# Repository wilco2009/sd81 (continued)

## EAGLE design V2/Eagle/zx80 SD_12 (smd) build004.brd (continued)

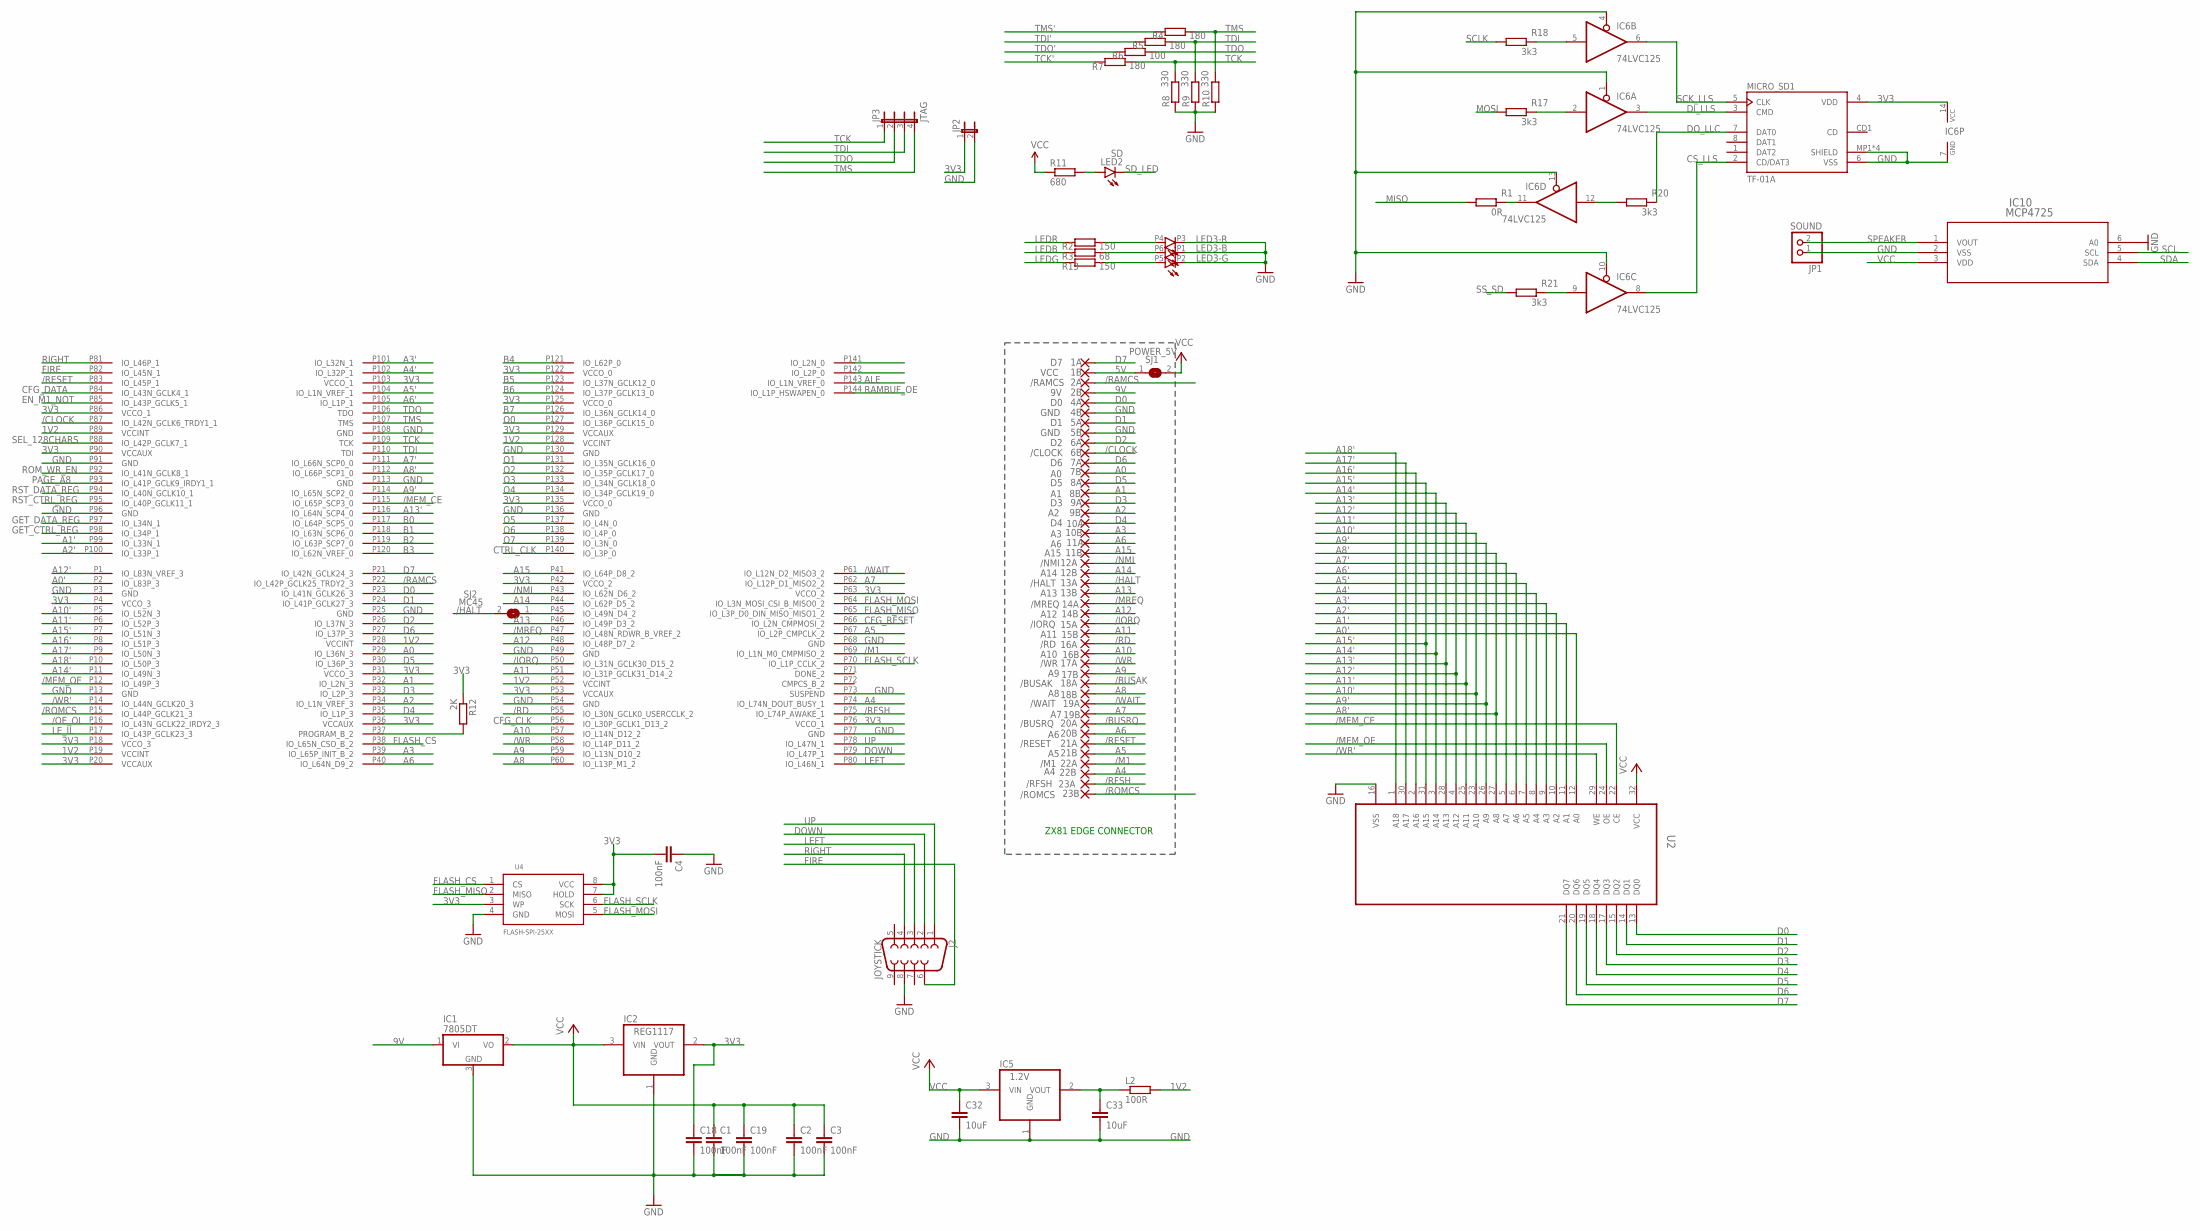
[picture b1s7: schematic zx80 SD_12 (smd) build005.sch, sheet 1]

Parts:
1A: D7; EDGEPIN
1B: VCC; EDGEPIN
2A: /RAMCS; EDGEPIN
2B: 9V; EDGEPIN
4A: D0; EDGEPIN
4B, 5B: GND; EDGEPIN
5A: D1; EDGEPIN
6A: D2; EDGEPIN
6B: /CLOCK; EDGEPIN
7A: D6; EDGEPIN
7B: A0; EDGEPIN
8A: D5; EDGEPIN
8B: A1; EDGEPIN
9A: D3; EDGEPIN
9B: A2; EDGEPIN
10A: D4; EDGEPIN
10B: A3; EDGEPIN
11A, 20B: A6; EDGEPIN
11B: A15; EDGEPIN
12A: /NMI; EDGEPIN
12B: A14; EDGEPIN
13A: /HALT; EDGEPIN
13B: A13; EDGEPIN
14A: /MREQ; EDGEPIN
14B: A12; EDGEPIN
15A: /IORQ; EDGEPIN
15B: A11; EDGEPIN
16A: /RD; EDGEPIN
16B: A10; EDGEPIN
17A: /WR; EDGEPIN
17B: A9; EDGEPIN
18A: /BUSAK; EDGEPIN
18B: A8; EDGEPIN
19A: /WAIT; EDGEPIN
19B: A7; EDGEPIN
20A: /BUSRQ; EDGEPIN
21A: /RESET; EDGEPIN
21B: A5; EDGEPIN
22A: /M1; EDGEPIN
22B: A4; EDGEPIN
23A: /RFSH; EDGEPIN
23B: /ROMCS; EDGEPIN
C1, C2, C3, C18, C19: 100nF; C0603
C4: 100nF; C0603K
C32, C33: 10uF; C0603K
IC1: 7805DT; TO252
IC2: REG1117; SOT223
IC5: 1.2V; SOT223
IC6: 74LVC125; SO14
IC10: MCP4725; SOT-23-6_MC
J2: JOYSTICK; DB9_MALE
JP1: SOUND; 1X02
JP2: JP1E; JP1
JP3: JTAG; JP4
L2: 100R; R0603
LED2: SD; CHIPLED_0603
LED3: STATUS; 3535-PLCC6
MICRO_SD1: TF-01A
R1: 0R; R0603
R2, R13: 150; R0603
R3: 68; R0603
R4, R5, R7: 180; R0603
R6: 100; R0603
R8, R9, R10: 330; R0603
R11: 680; R0603
R12: 2K; R0603
R17, R18, R20, R21: 3k3; R0603
SJ1: POWER_5V; SJ
SJ2: MC45; SJ
U2: AS6C4008; SOP32-5
U4: FLASH-SPI-25XX; SO08-EIAJ
U$1: XC6SLX9-2TQG144C; TQ144

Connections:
3V3: C4.2, C18.1, IC2.2 (VOUT), IC6.14 (VCC), JP2.1, MICRO_SD1.4 (VDD), R12.1, U4.3 (WP), U4.7 (HOLD), U4.8 (VCC), U$1.P4 (VCCO_3), U$1.P18 (VCCO_3), U$1.P20 (VCCAUX), U$1.P31 (VCCO_3), U$1.P36 (VCCAUX), U$1.P42 (VCCO_2), U$1.P53 (VCCAUX), U$1.P63 (VCCO_2), U$1.P76 (VCCO_1), U$1.P86 (VCCO_1), U$1.P90 (VCCAUX), U$1.P103 (VCCO_1), U$1.P122 (VCCO_0), U$1.P125 (VCCO_0), U$1.P129 (VCCAUX), U$1.P135 (VCCO_0); also elsewhere on the board
5V: 1B.1, SJ1.1
9V: 2B.1, IC1.1 (VI)
/BUSAK: 18A.1
/BUSRQ: 20A.1
/CLOCK: 6B.1, U$1.P87 (IO_L42N_GCLK6_TRDY1_1); also elsewhere on the board
/HALT: 13A.1, SJ2.2
/IORQ: 15A.1, U$1.P50 (IO_L31N_GCLK30_D15_2); also elsewhere on the board
/M1: 22A.1, U$1.P69 (IO_L1N_M0_CMPMISO_2); also elsewhere on the board
/MEM_CE: U2.22 (CE), U$1.P115 (IO_L65P_SCP3_0); also elsewhere on the board
/MEM_OE: U2.24 (OE), U$1.P12 (IO_L49P_3); also elsewhere on the board
/MREQ: 14A.1, U$1.P47 (IO_L48N_RDWR_B_VREF_2); also elsewhere on the board
/NMI: 12A.1, U$1.P43 (IO_L62N_D6_2); also elsewhere on the board
/RAMCS: 2A.1, U$1.P22 (IO_L42P_GCLK25_TRDY2_3); also elsewhere on the board
/RD: 16A.1, U$1.P55 (IO_L30N_GCLK0_USERCCLK_2); also elsewhere on the board
/RESET: 21A.1, U$1.P83 (IO_L45P_1); also elsewhere on the board
/RFSH: 23A.1, U$1.P75 (IO_L74P_AWAKE_1); also elsewhere on the board
/ROMCS: 23B.1, U$1.P15 (IO_L44P_GCLK21_3); also elsewhere on the board
/WAIT: 19A.1, U$1.P61 (IO_L12N_D2_MISO3_2); also elsewhere on the board
/WR: 17A.1, U$1.P58 (IO_L14P_D11_2); also elsewhere on the board
/WR': U2.29 (WE), U$1.P14 (IO_L44N_GCLK20_3); also elsewhere on the board
A0: 7B.1, U$1.P29 (IO_L36N_3); also elsewhere on the board
A0': U2.12 (A0), U$1.P2 (IO_L83P_3); also elsewhere on the board
A1: 8B.1, U$1.P32 (IO_L2N_3); also elsewhere on the board
A1': U2.11 (A1), U$1.P99 (IO_L33N_1); also elsewhere on the board
A2: 9B.1, U$1.P34 (IO_L1N_VREF_3); also elsewhere on the board
A2': U2.10 (A2), U$1.P100 (IO_L33P_1); also elsewhere on the board
A3: 10B.1, U$1.P39 (IO_L65P_INIT_B_2); also elsewhere on the board
A3': U2.9 (A3), U$1.P101 (IO_L32N_1); also elsewhere on the board
A4: 22B.1, U$1.P74 (IO_L74N_DOUT_BUSY_1); also elsewhere on the board
A4': U2.8 (A4), U$1.P102 (IO_L32P_1); also elsewhere on the board
A5: 21B.1, U$1.P67 (IO_L2P_CMPCLK_2); also elsewhere on the board
A5': U2.7 (A5), U$1.P104 (IO_L1N_VREF_1); also elsewhere on the board
A6: 11A.1, 20B.1, U$1.P40 (IO_L64N_D9_2); also elsewhere on the board
A6': U2.6 (A6), U$1.P105 (IO_L1P_1); also elsewhere on the board
A7: 19B.1, U$1.P62 (IO_L12P_D1_MISO2_2); also elsewhere on the board
A7': U2.5 (A7), U$1.P111 (IO_L66N_SCP0_0); also elsewhere on the board
A8: 18B.1, U$1.P60 (IO_L13P_M1_2); also elsewhere on the board
A8': U2.27 (A8), U$1.P112 (IO_L66P_SCP1_0); also elsewhere on the board
A9: 17B.1, U$1.P59 (IO_L13N_D10_2); also elsewhere on the board
A9': U2.26 (A9), U$1.P114 (IO_L65N_SCP2_0); also elsewhere on the board
A10: 16B.1, U$1.P57 (IO_L14N_D12_2); also elsewhere on the board
A10': U2.23 (A10), U$1.P5 (IO_L52N_3); also elsewhere on the board
A11: 15B.1, U$1.P51 (IO_L31P_GCLK31_D14_2); also elsewhere on the board
A11': U2.25 (A11), U$1.P6 (IO_L52P_3); also elsewhere on the board
A12: 14B.1, U$1.P48 (IO_L48P_D7_2); also elsewhere on the board
A12': U2.4 (A12), U$1.P1 (IO_L83N_VREF_3); also elsewhere on the board
A13: 13B.1, U$1.P46 (IO_L49P_D3_2); also elsewhere on the board
A13': U2.28 (A13), U$1.P116 (IO_L64N_SCP4_0); also elsewhere on the board
A14: 12B.1, U$1.P44 (IO_L62P_D5_2); also elsewhere on the board
A14': U2.3 (A14), U$1.P11 (IO_L49N_3); also elsewhere on the board
A15: 11B.1, U$1.P41 (IO_L64P_D8_2); also elsewhere on the board
A15': U2.31 (A15), U$1.P7 (IO_L51N_3); also elsewhere on the board
A16': U2.2 (A16), U$1.P8 (IO_L51P_3); also elsewhere on the board
A17': U2.30 (A17), U$1.P9 (IO_L50N_3); also elsewhere on the board
A18': U2.1 (A18), U$1.P10 (IO_L50P_3); also elsewhere on the board
CS_LLS: IC6.8 (O), MICRO_SD1.2 (CD/DAT3)
D0: 4A.1, U2.13 (DQ0), U$1.P23 (IO_L41N_GCLK26_3); also elsewhere on the board
D1: 5A.1, U2.14 (DQ1), U$1.P24 (IO_L41P_GCLK27_3); also elsewhere on the board
D2: 6A.1, U2.15 (DQ2), U$1.P26 (IO_L37N_3); also elsewhere on the board
D3: 9A.1, U2.17 (DQ3), U$1.P33 (IO_L2P_3); also elsewhere on the board
D4: 10A.1, U2.18 (DQ4), U$1.P35 (IO_L1P_3); also elsewhere on the board
D5: 8A.1, U2.19 (DQ5), U$1.P30 (IO_L36P_3); also elsewhere on the board
D6: 7A.1, U2.20 (DQ6), U$1.P27 (IO_L37P_3); also elsewhere on the board
D7: 1A.1, U2.21 (DQ7), U$1.P21 (IO_L42N_GCLK24_3); also elsewhere on the board
DI_LLS: IC6.3 (O), MICRO_SD1.3 (CMD)
DOWN: J2.2, U$1.P79 (IO_L47P_1); also elsewhere on the board
DO_LLC: IC6.12 (I), R20.1
FIRE: J2.6, U$1.P82 (IO_L45N_1); also elsewhere on the board
LEDB: R3.1; also elsewhere on the board
LEDG: R13.1; also elsewhere on the board
LEDR: R2.1; also elsewhere on the board
LEFT: J2.3, U$1.P80 (IO_L46N_1); also elsewhere on the board
MISO: R1.1; also elsewhere on the board
MOSI: R17.1; also elsewhere on the board
unnamed: IC6.2 (I), R17.2
unnamed: IC6.11 (O), R1.2
unnamed: IC6.5 (I), R18.2
unnamed: MICRO_SD1.7 (DAT0), R20.2
unnamed: IC6.9 (I), R21.2
unnamed: LED2.A, R11.2
unnamed: LED3.P4 (A), R2.2
unnamed: LED3.P6 (A), R3.2
unnamed: LED3.P5 (A), R13.2
unnamed: L2.2, U$1.P19 (VCCINT), U$1.P28 (VCCINT), U$1.P52 (VCCINT), U$1.P89 (VCCINT), U$1.P128 (VCCINT)
unnamed: R12.2, U$1.P37 (PROGRAM_B_2)
unnamed: U4.1 (CS), U$1.P38 (IO_L65N_CSO_B_2)
unnamed: U4.5 (MOSI), U$1.P64 (IO_L3N_MOSI_CSI_B_MISO0_2)
unnamed: U4.2 (MISO), U$1.P65 (IO_L3P_D0_DIN_MISO_MISO1_2)
unnamed: U4.6 (SCK), U$1.P70 (IO_L1P_CCLK_2)
RIGHT: J2.4, U$1.P81 (IO_L46P_1); also elsewhere on the board
SCK_LLS: IC6.6 (O), MICRO_SD1.5 (CLK)
SCLK: R18.1; also elsewhere on the board
SD_LED: LED2.C; also elsewhere on the board
SPEAKER: IC10.1 (VOUT), JP1.2
SS_SD: R21.1; also elsewhere on the board
TCK: JP3.1, R7.2, R8.2, U$1.P109 (TCK); also elsewhere on the board
TCK': R7.1; also elsewhere on the board
TDI: JP3.3, R5.2, R9.2, U$1.P110 (TDI); also elsewhere on the board
TDI': R5.1; also elsewhere on the board
TDO: JP3.2, R6.2, U$1.P106 (TDO); also elsewhere on the board
TDO': R6.1; also elsewhere on the board
TMS: JP3.4, R4.2, R10.2, U$1.P107 (TMS); also elsewhere on the board
TMS': R4.1; also elsewhere on the board
UP: J2.1, U$1.P78 (IO_L47N_1); also elsewhere on the board

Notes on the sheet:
ZX81 EDGE CONNECTOR

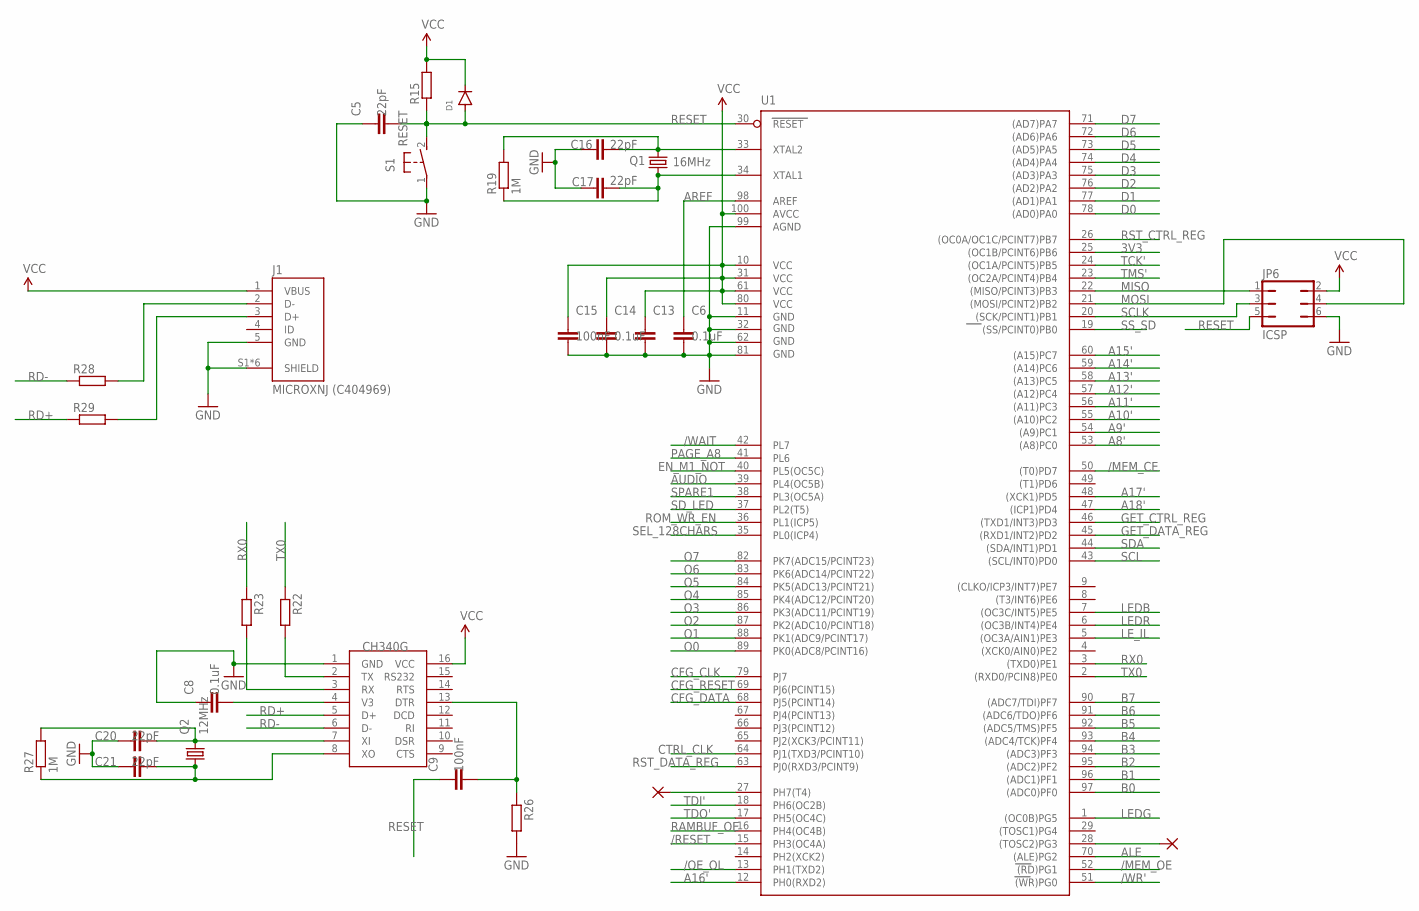
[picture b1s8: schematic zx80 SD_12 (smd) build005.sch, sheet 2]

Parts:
C5, C16, C17, C20, C21: 22pF; C0603
C6, C8, C13, C14: 0.1uF; C0603
C9, C15: 100nF; C0603
D1: DIODE-SOD123; SOD123
IC7: CH340G; SOIC16
J1: MICROXNJ (C404969); SHOUHAN_MICROXNJ
JP6: ICSP; JP3Q
PAD2: PH7; 1,6/0,8
PAD3: PG3; 1,6/0,8
Q1: 16MHz; 3.2X2.5_KX-7
Q2: 12MHz; 3.2X2.5_KX-7
R15: R0603
R19, R27: 1M; R0603
R22, R23, R26: 1K; R0603
R28, R29: 22R; R0603
S1: RESET; B3F-31XX
U1: ATMEGA2560AU; TQFP100

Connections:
3V3: U1.25 ((OC1B/PCINT6)PB6); also elsewhere on the board
/MEM_CE: U1.50 ((T0)PD7); also elsewhere on the board
/MEM_OE: U1.52 ((RD)PG1); also elsewhere on the board
/RESET: U1.15 (PH3(OC4A)); also elsewhere on the board
/WAIT: U1.42 (PL7); also elsewhere on the board
/WR': U1.51 ((WR)PG0); also elsewhere on the board
A8': U1.53 ((A8)PC0); also elsewhere on the board
A9': U1.54 ((A9)PC1); also elsewhere on the board
A10': U1.55 ((A10)PC2); also elsewhere on the board
A11': U1.56 ((A11)PC3); also elsewhere on the board
A12': U1.57 ((A12)PC4); also elsewhere on the board
A13': U1.58 ((A13)PC5); also elsewhere on the board
A14': U1.59 ((A14)PC6); also elsewhere on the board
A15': U1.60 ((A15)PC7); also elsewhere on the board
A16': U1.12 (PH0(RXD2)); also elsewhere on the board
A17': U1.48 ((XCK1)PD5); also elsewhere on the board
A18': U1.47 ((ICP1)PD4); also elsewhere on the board
ALE: U1.70 ((ALE)PG2); also elsewhere on the board
AREF: C6.1, U1.98 (AREF)
AUDIO: U1.39 (PL4(OC5B))
B0: U1.97 ((ADC0)PF0); also elsewhere on the board
B1: U1.96 ((ADC1)PF1); also elsewhere on the board
B2: U1.95 ((ADC2)PF2); also elsewhere on the board
B3: U1.94 ((ADC3)PF3); also elsewhere on the board
B4: U1.93 ((ADC4/TCK)PF4); also elsewhere on the board
B5: U1.92 ((ADC5/TMS)PF5); also elsewhere on the board
B6: U1.91 ((ADC6/TDO)PF6); also elsewhere on the board
B7: U1.90 ((ADC7/TDI)PF7); also elsewhere on the board
CFG_CLK: U1.79 (PJ7); also elsewhere on the board
CFG_DATA: U1.68 (PJ5(PCINT14)); also elsewhere on the board
CFG_RESET: U1.69 (PJ6(PCINT15)); also elsewhere on the board
CTRL_CLK: U1.64 (PJ1(TXD3/PCINT10)); also elsewhere on the board
D0: U1.78 ((AD0)PA0); also elsewhere on the board
D1: U1.77 ((AD1)PA1); also elsewhere on the board
D2: U1.76 ((AD2)PA2); also elsewhere on the board
D3: U1.75 ((AD3)PA3); also elsewhere on the board
D4: U1.74 ((AD4)PA4); also elsewhere on the board
D5: U1.73 ((AD5)PA5); also elsewhere on the board
D6: U1.72 ((AD6)PA6); also elsewhere on the board
D7: U1.71 ((AD7)PA7); also elsewhere on the board
EN_M1_NOT: U1.40 (PL5(OC5C)); also elsewhere on the board
GET_CTRL_REG: U1.46 ((TXD1/INT3)PD3); also elsewhere on the board
GET_DATA_REG: U1.45 ((RXD1/INT2)PD2); also elsewhere on the board
LEDB: U1.7 ((OC3C/INT5)PE5); also elsewhere on the board
LEDG: U1.1 ((OC0B)PG5); also elsewhere on the board
LEDR: U1.6 ((OC3B/INT4)PE4); also elsewhere on the board
LE_IL: U1.5 ((OC3A/AIN1)PE3); also elsewhere on the board
MISO: JP6.1, U1.22 ((MISO/PCINT3)PB3); also elsewhere on the board
MOSI: JP6.4, U1.21 ((MOSI/PCINT2)PB2); also elsewhere on the board
unnamed: PAD2.1, U1.27 (PH7(T4))
unnamed: IC7.2 (TX), R22.2
unnamed: PAD3.1, U1.28 ((TOSC2)PG3)
unnamed: IC7.3 (RX), R23.2
unnamed: C8.2, IC7.4 (V3)
unnamed: C20.2, IC7.7 (XI), Q2.3 (2), R27.2
unnamed: C21.2, IC7.8 (XO), Q2.1, R27.1
unnamed: C16.2, Q1.3 (2), R19.2, U1.33 (XTAL2)
unnamed: C17.2, Q1.1, R19.1, U1.34 (XTAL1)
unnamed: C9.2, IC7.13 (DTR), R26.1
unnamed: J1.2 (D-), R28.2
unnamed: J1.3 (D+), R29.2
O0: U1.89 (PK0(ADC8/PCINT16)); also elsewhere on the board
O1: U1.88 (PK1(ADC9/PCINT17)); also elsewhere on the board
O2: U1.87 (PK2(ADC10/PCINT18)); also elsewhere on the board
O3: U1.86 (PK3(ADC11/PCINT19)); also elsewhere on the board
O4: U1.85 (PK4(ADC12/PCINT20)); also elsewhere on the board
O5: U1.84 (PK5(ADC13/PCINT21)); also elsewhere on the board
PAGE_A8: U1.41 (PL6); also elsewhere on the board
RD+: IC7.5 (D+), R29.1
RD-: IC7.6 (D-), R28.1
RESET: C5.2, C9.1, D1.A, JP6.5, R15.1, S1.2 (S), U1.30 (RESET)
ROM_WR_EN: U1.36 (PL1(ICP5)); also elsewhere on the board
RST_CTRL_REG: U1.26 ((OC0A/OC1C/PCINT7)PB7); also elsewhere on the board
RST_DATA_REG: U1.63 (PJ0(RXD3/PCINT9)); also elsewhere on the board
RX0: R23.1, U1.3 ((TXD0)PE1)
SCLK: JP6.3, U1.20 ((SCK/PCINT1)PB1); also elsewhere on the board
SD_LED: U1.37 (PL2(T5)); also elsewhere on the board
SEL_128CHARS: U1.35 (PL0(ICP4)); also elsewhere on the board
SPARE1: U1.38 (PL3(OC5A)); also elsewhere on the board
SS_SD: U1.19 ((SS/PCINT0)PB0); also elsewhere on the board
TCK': U1.24 ((OC1A/PCINT5)PB5); also elsewhere on the board
TDI': U1.18 (PH6(OC2B)); also elsewhere on the board
TDO': U1.17 (PH5(OC4C)); also elsewhere on the board
TMS': U1.23 ((OC2A/PCINT4)PB4); also elsewhere on the board
TX0: R22.1, U1.2 ((RXD0/PCIN8)PE0)

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
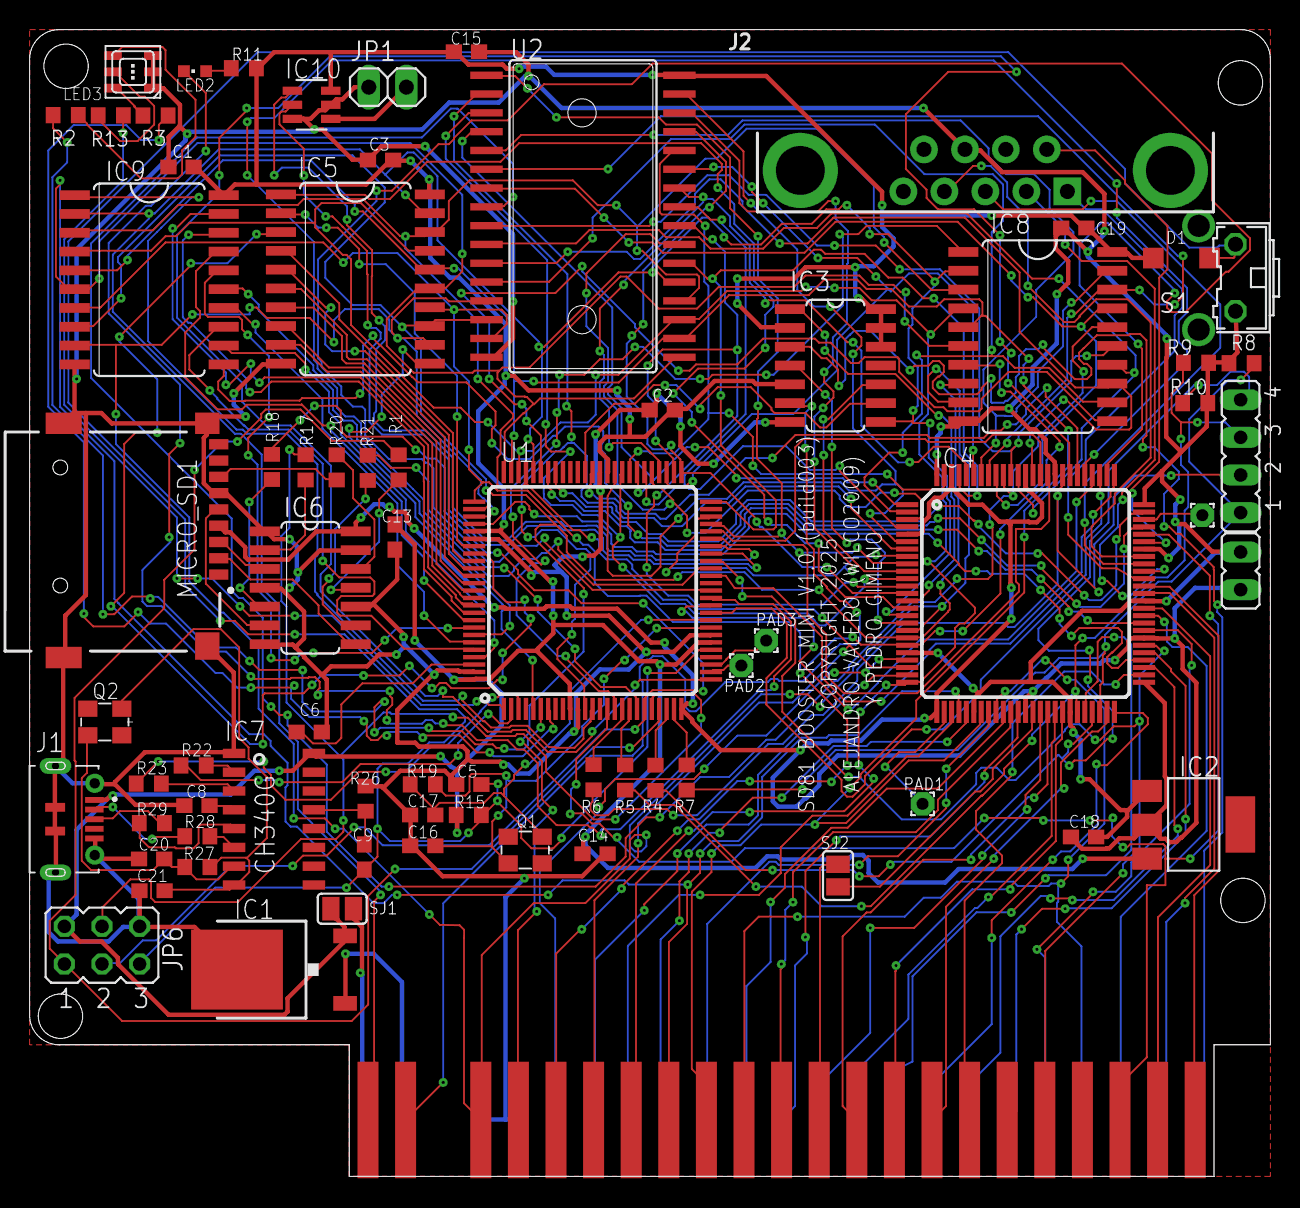
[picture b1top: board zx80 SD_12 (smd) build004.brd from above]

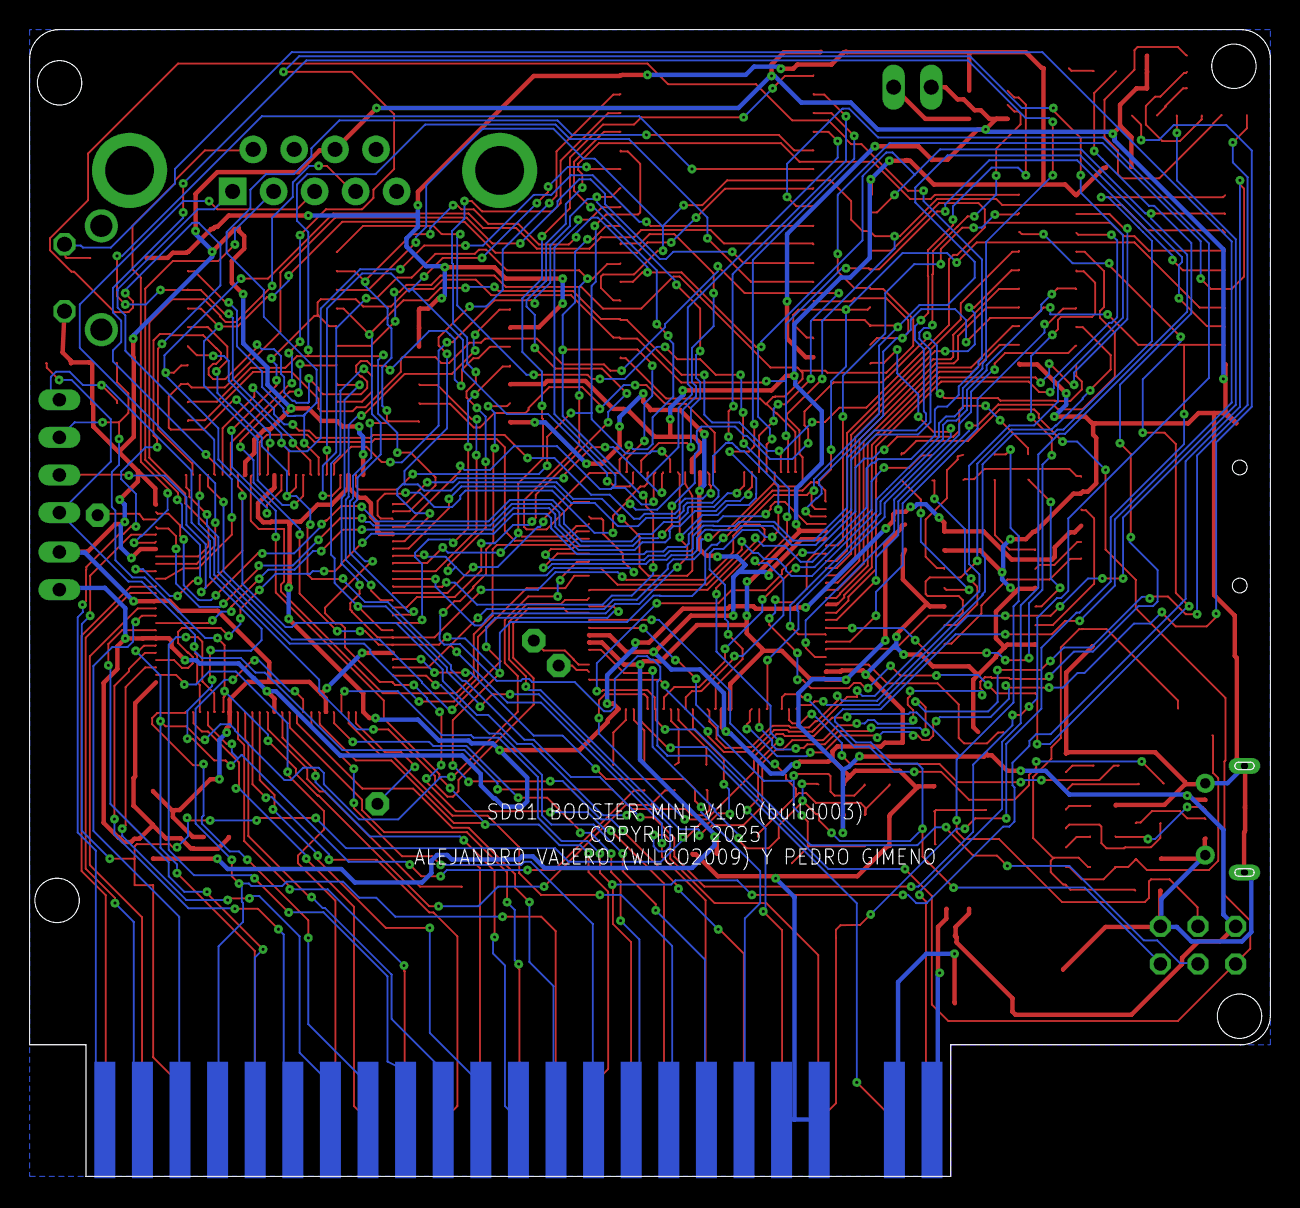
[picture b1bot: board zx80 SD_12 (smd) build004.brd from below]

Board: 2 copper layers, 83.8 x 77.5 mm, 115 parts (22 on the bottom side), 160 nets.

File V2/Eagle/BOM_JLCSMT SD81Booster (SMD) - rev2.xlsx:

Comment | Designator | Footprint | JLCPCB Part #（optional）
100nF | C1 | C0603 | C14663
100nF | C2 | C0603 | C14663
100nF | C3 | C0603 | C14663
22pF | C5 | C0603 | C1653
100nF | C6 | C0603 | C14663
100nF | C8 | C0603 | C14663
100nF | C9 | C0603 | C14663
100nF | C13 | C0603 | C14663
100nF | C14 | C0603 | C14663
100nF | C15 | C0603 | C14663
22pF | C16 | C0603 | C1653
22pF | C17 | C0603 | C1653
100nF | C18 | C0603 | C14663
100nF | C19 | C0603 | C14663
22pF | C20 | C0603 | C91701
22pF | C21 | C0603 | C91701
1n4148 | D1 | SOD123 | C81598
7805 | IC1 | TO252
REG1117 | IC2 | SOT223 | C5400
74ACT125D | IC3 | SO14 | C113254
XC95144XL-10TQG100C | IC4 | TQFP100 | C45126
74HC573D | IC5 | SO20W | C5122488
74LVC125 | IC6 | SO14 | C7661
CH340G | IC7 | SOIC16 | C14267
74HC573D | IC8 | SO20W | C5122488
74HC573D | IC9 | SO20W | C5122488
MICROXNJ (C404969) | J1 | SHOUHAN_MICROXNJ | C404969
DB9 | J2
ICSP | JP6 | JP3Q | C124384
KT-0603B | LED2 | D603 | C7496819
RS-3535MWAR | LED3 | SMD3535 | C110402
TF-01A | MICRO_SD1 | TF-01A | C2889258
16MHz | Q1 | 3,2X2,5_KX-7 | C280836
12MHz | Q2 | 3,2X2,5_KX-7 | C93234
0R | R1 | R0603 | C21189
150 | R2 | R0603 | C22808
68 | R3 | R0603 | C27592
180 | R4 | R0603 | C22828
180 | R5 | R0603 | C22828
100 | R6 | R0603 | C22775
180 | R7 | R0603 | C22828
330 | R8 | R0603 | C23138
330 | R9 | R0603 | C23138
330 | R10 | R0603 | C23138
680 | R11 | R0603 | C23228
150 | R13 | R0603 | C22808
10K | R15 | R0603 | C15401
3k3 | R17 | R0603 | C22978
3k3 | R18 | R0603 | C22978
1M | R19 | R0603 | C22935
3k3 | R20 | R0603 | C22978
3k3 | R21 | R0603 | C22978
1K | R22 | R0603 | C21190
1K | R23 | R0603 | C21190
1K | R26 | R0603 | C21190
1M | R27 | R0603 | C22935
22R | R28 | R0603 | C1203
22R | R29 | R0603 | C1203
RESET | S1 | B3F-31XX
ATMEGA2560AU | U1 | TQFP100 | C22460
AS6C4008-55SIN | U2 | SOIC127P1407X299-32N | C2952831
